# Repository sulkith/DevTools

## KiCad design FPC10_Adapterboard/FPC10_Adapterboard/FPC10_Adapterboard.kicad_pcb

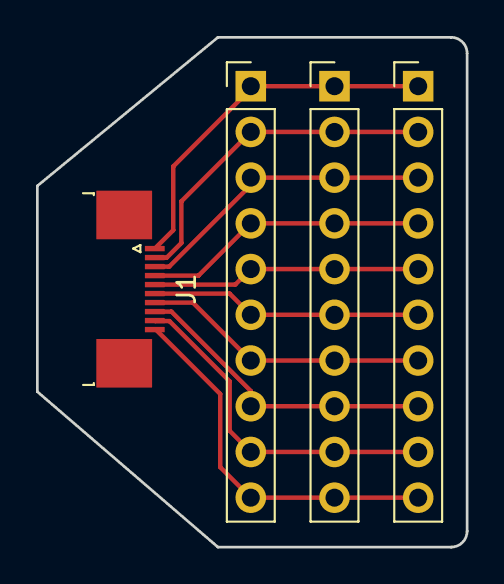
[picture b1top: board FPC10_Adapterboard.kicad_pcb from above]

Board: 2 copper layers, 23.9 x 28.3 mm, 4 parts (0 on the bottom side), 10 nets.

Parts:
J1: Conn_01x10_MountingPin; TE_1-1734839-0_1x10-1MP_P0.5mm_Horizontal
J2, J3, J4: Conn_01x10; PinHeader_1x10_P2.54mm_Vertical

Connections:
P1: J1.1, J2.1, J3.1, J4.1
P2: J1.2, J2.2, J3.2, J4.2
P3: J1.3, J2.3, J3.3, J4.3
P4: J1.4, J2.4, J3.4, J4.4
P5: J1.5, J2.5, J3.5, J4.5
P6: J1.6, J2.6, J3.6, J4.6
P7: J1.7, J2.7, J3.7, J4.7
P8: J1.8, J2.8, J3.8, J4.8
P9: J1.9, J2.9, J3.9, J4.9
P10: J1.10, J2.10, J3.10, J4.10

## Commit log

2020-07-17 Added FPC10 Adapterboard
